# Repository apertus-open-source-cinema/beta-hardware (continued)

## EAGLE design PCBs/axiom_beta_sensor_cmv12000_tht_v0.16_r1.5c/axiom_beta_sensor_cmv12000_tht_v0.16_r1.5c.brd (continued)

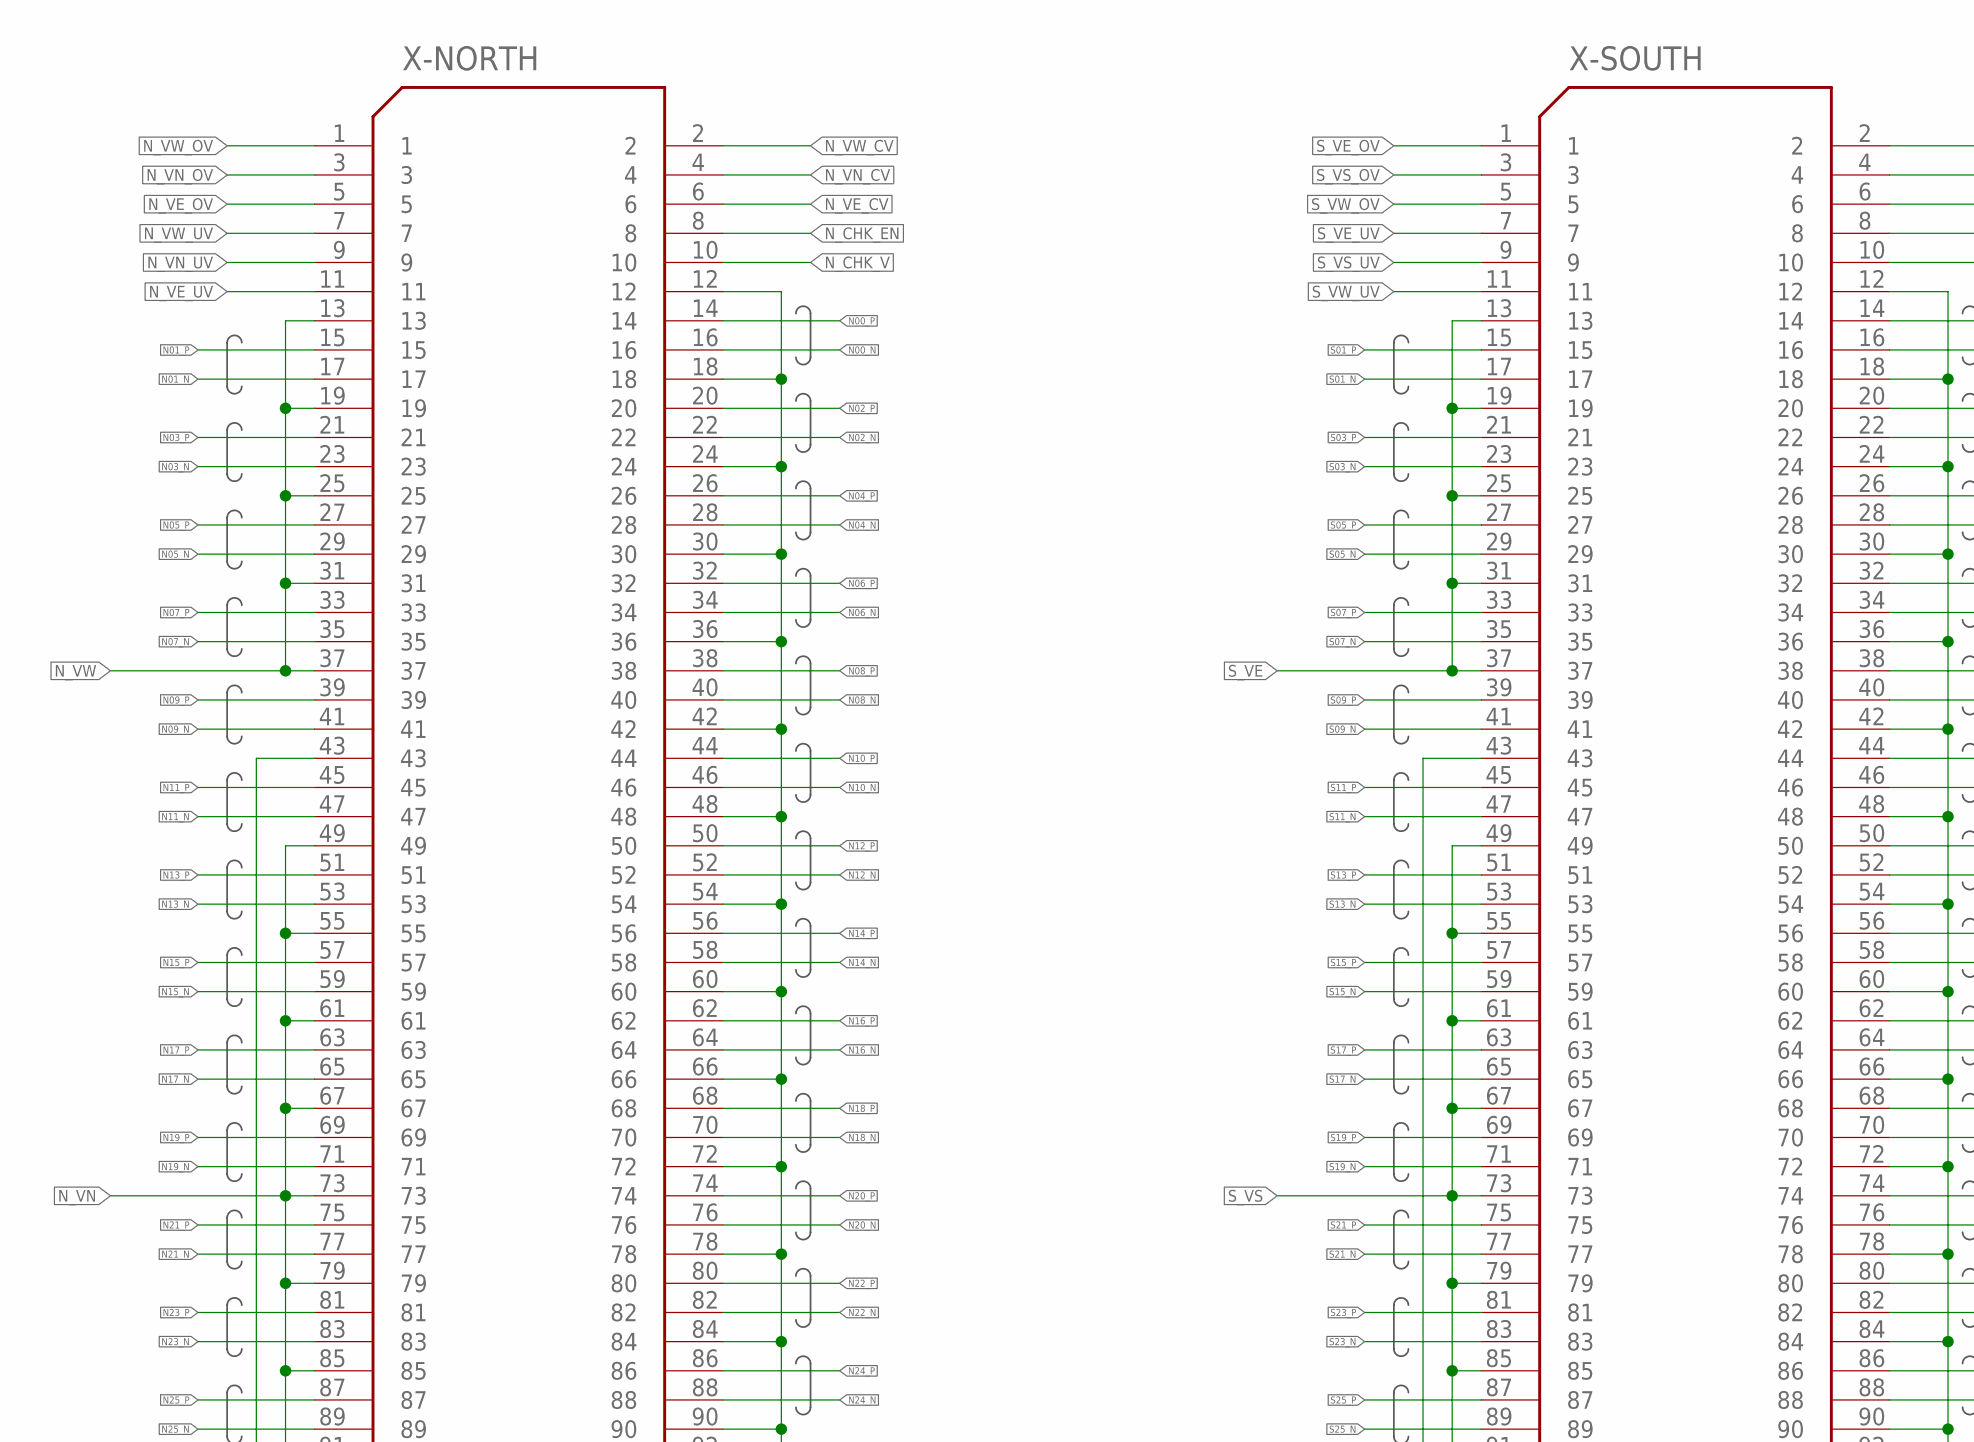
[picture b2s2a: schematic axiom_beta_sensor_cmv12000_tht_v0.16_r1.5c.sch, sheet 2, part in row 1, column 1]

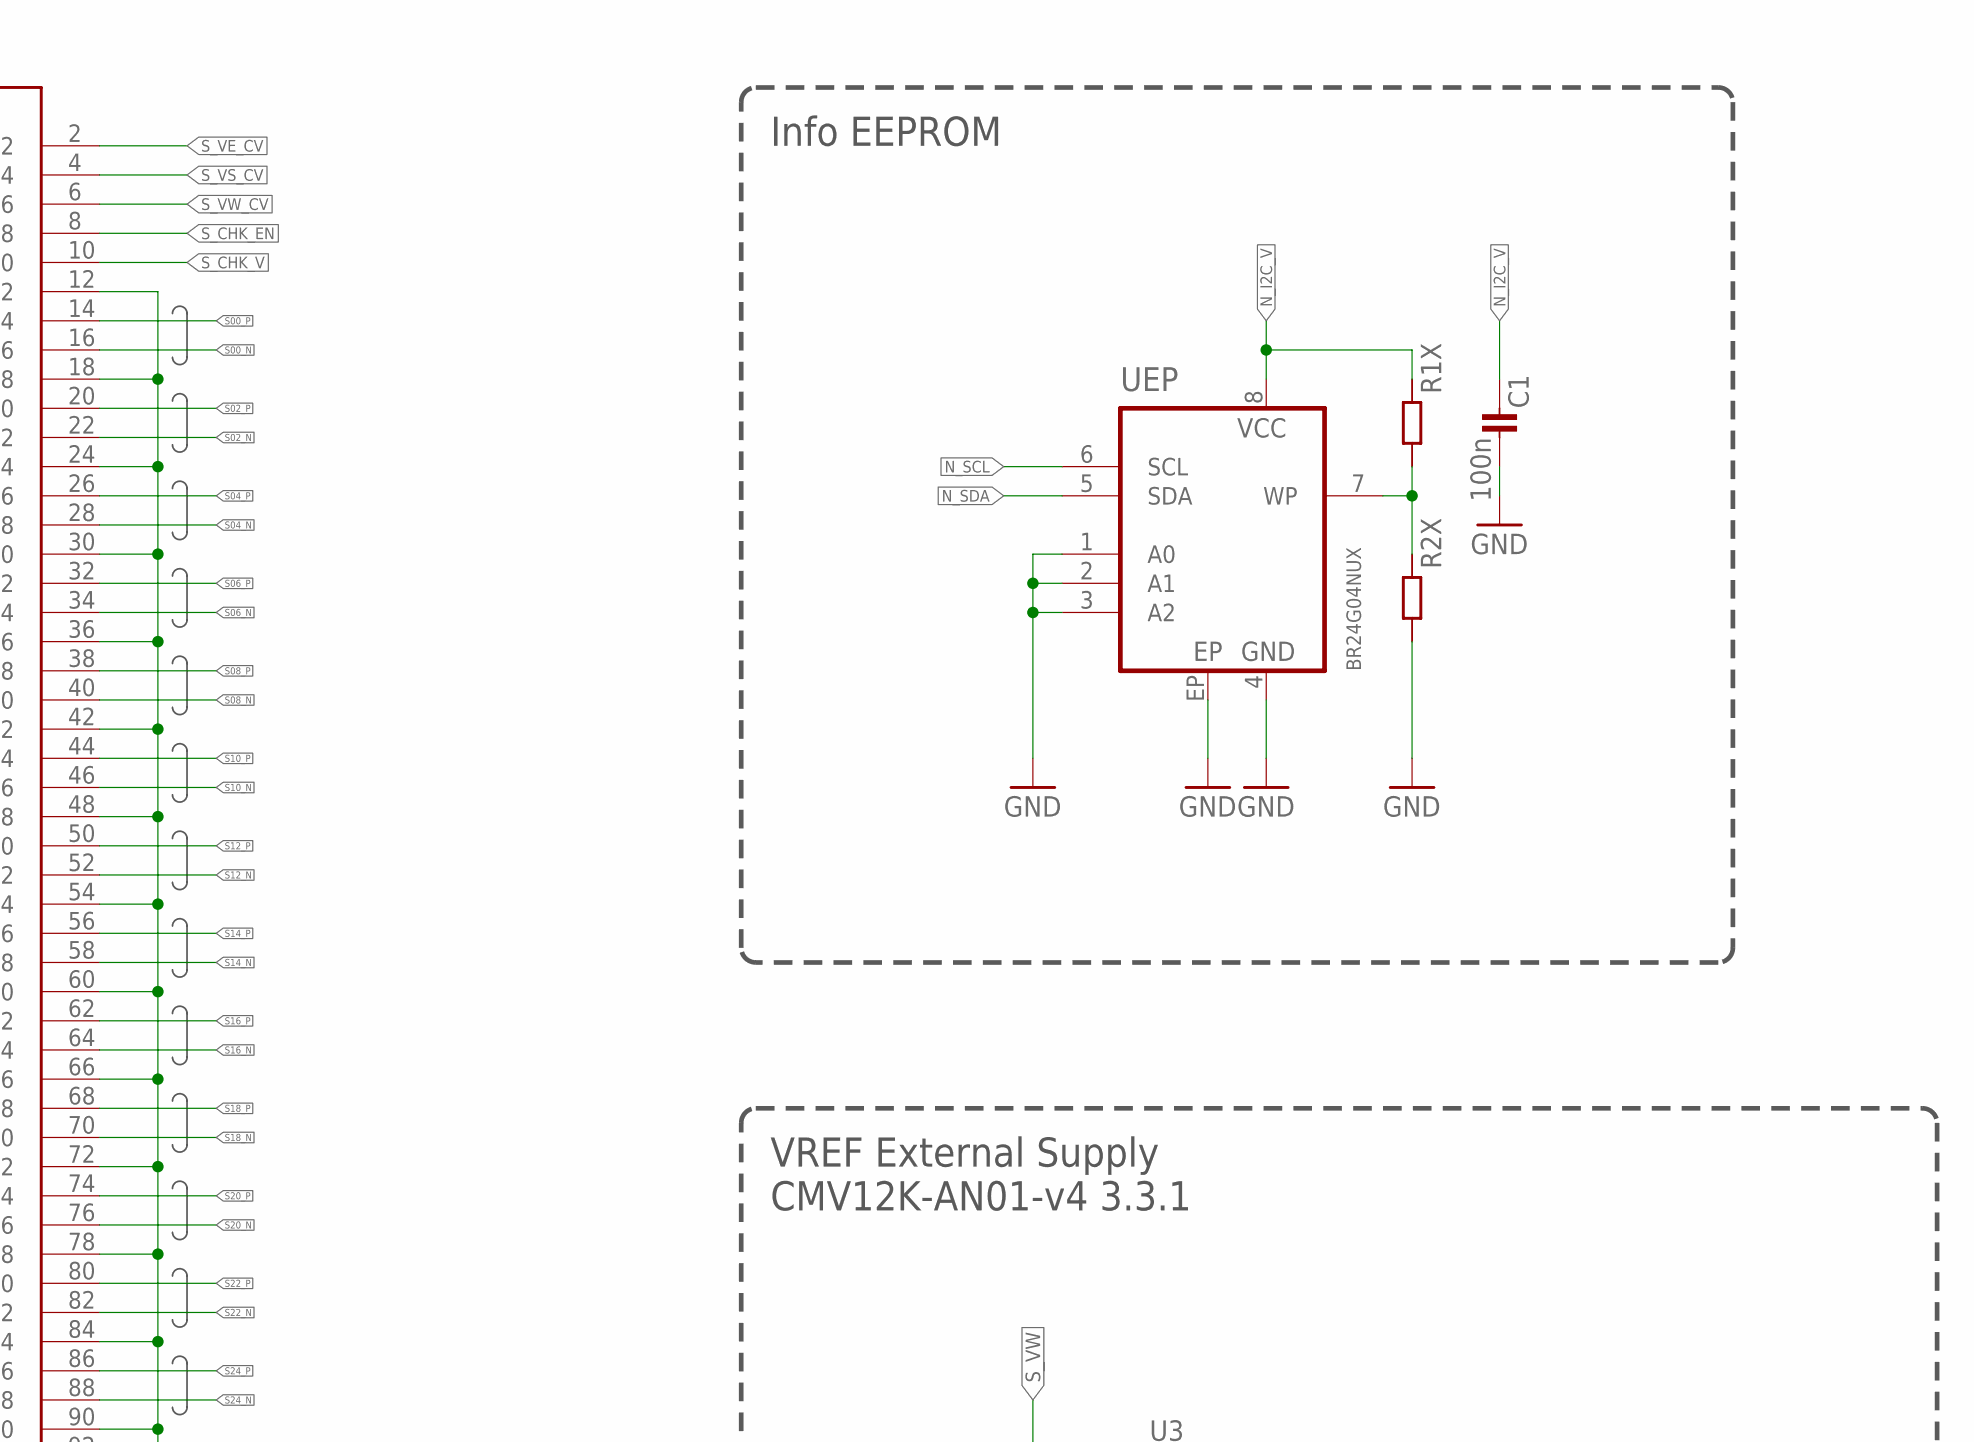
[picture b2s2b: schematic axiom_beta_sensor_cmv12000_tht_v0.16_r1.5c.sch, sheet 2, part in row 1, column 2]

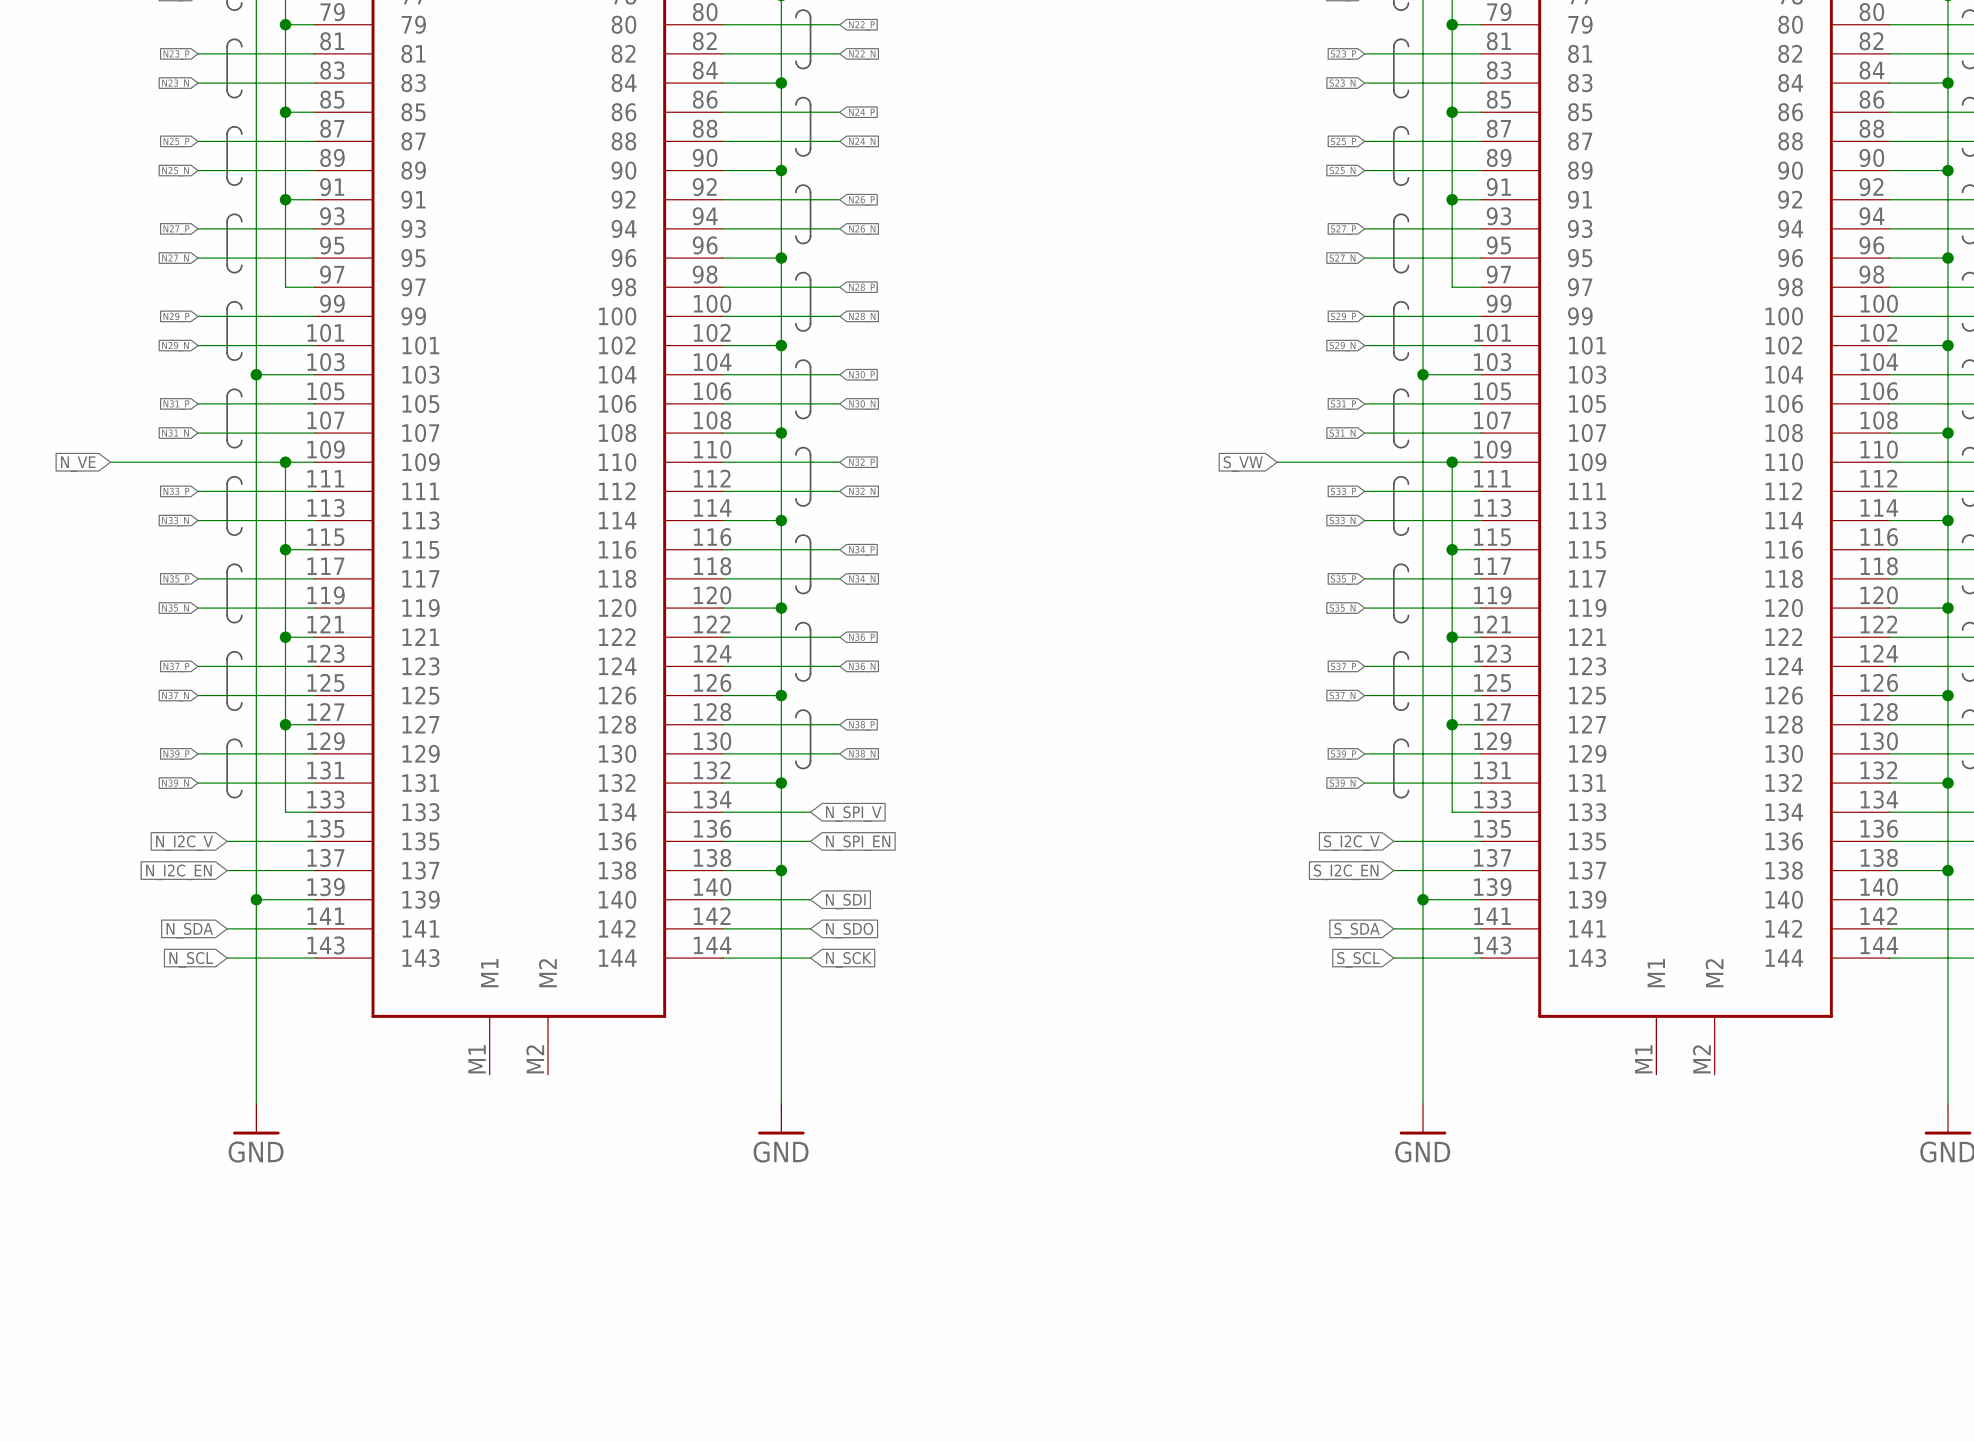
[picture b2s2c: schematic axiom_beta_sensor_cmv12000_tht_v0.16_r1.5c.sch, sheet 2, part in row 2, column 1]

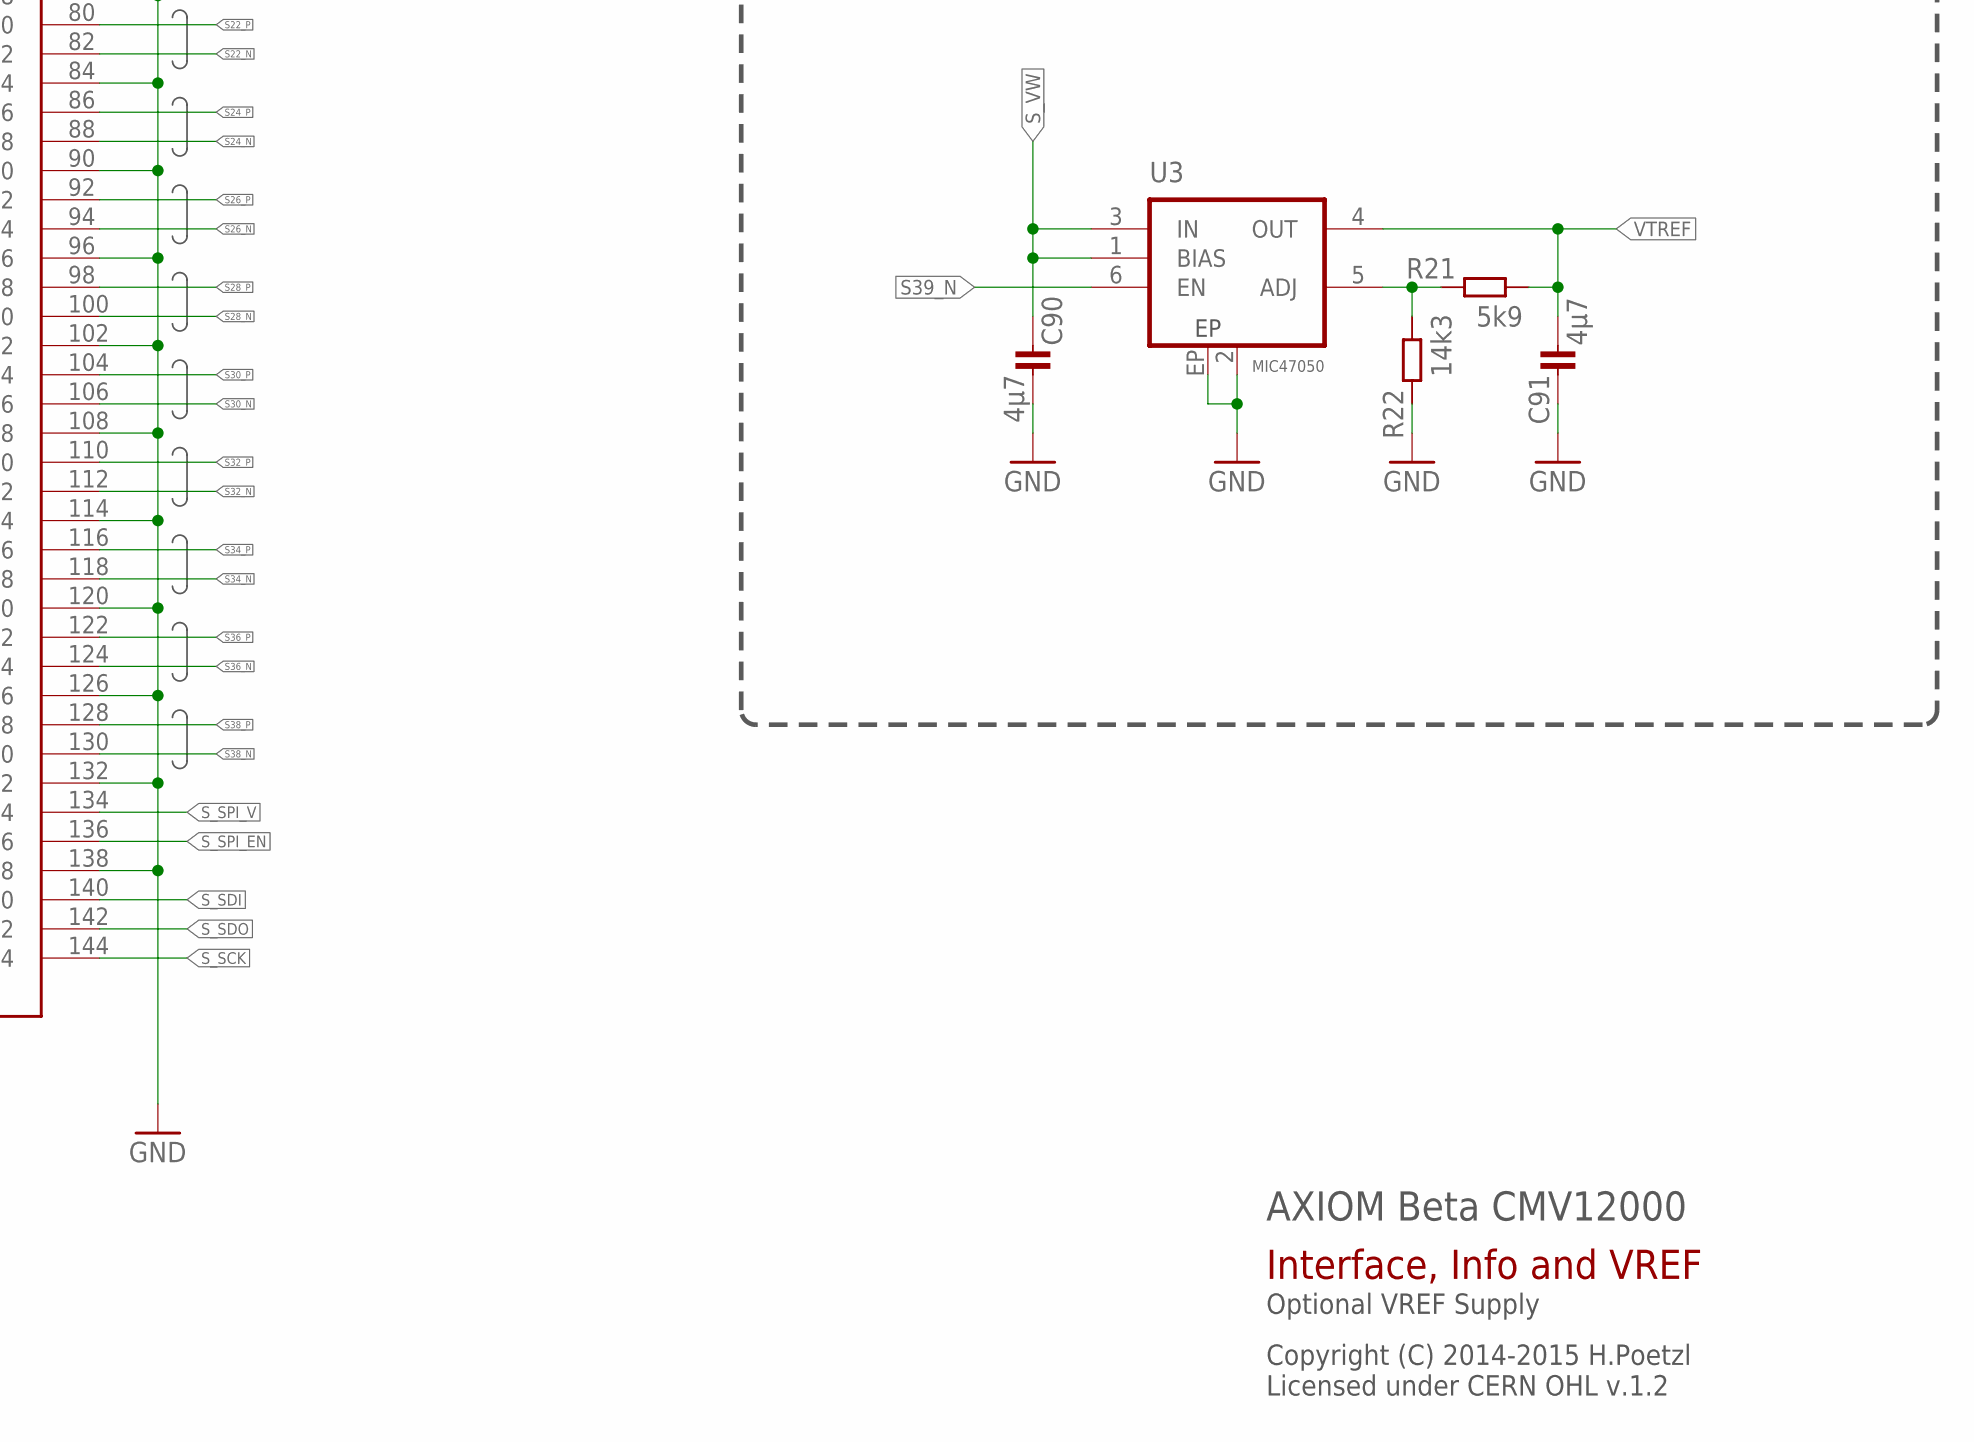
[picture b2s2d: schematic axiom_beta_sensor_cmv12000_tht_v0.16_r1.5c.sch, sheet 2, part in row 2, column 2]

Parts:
C1: 100n; 0402-C
C90, C91: 4µ7; 0402-C
R1X, R2X: R0402-C; 0402-C
R21: 5k9; 0402-C
R22: 14k3; 0402-C
U3: MIC47050; MLF-6
UEP: BR24G04NUX; DFN200X300X100-9N
X-NORTH: FX10-144P; FX10A-144P
X-SOUTH: FX10-144P; FX10A-144P

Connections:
GND: C1.2, C90.2, C91.1, R2X.2, R22.1, U3.2 (GND), U3.EP, UEP.1 (A0), UEP.2 (A1), UEP.3 (A2), UEP.4 (GND), UEP.EP, X-NORTH.12, X-NORTH.18, X-NORTH.24, X-NORTH.30, X-NORTH.36, X-NORTH.42, X-NORTH.43, X-NORTH.48, X-NORTH.54, X-NORTH.60, X-NORTH.66, X-NORTH.72, X-NORTH.78, X-NORTH.84, X-NORTH.90, X-NORTH.96, X-NORTH.102, X-NORTH.103, X-NORTH.108, X-NORTH.114, X-NORTH.120, X-NORTH.126, X-NORTH.132, X-NORTH.138, X-NORTH.139, X-SOUTH.12, X-SOUTH.18, X-SOUTH.24, X-SOUTH.30, X-SOUTH.36, X-SOUTH.42, X-SOUTH.43, X-SOUTH.48, X-SOUTH.54, X-SOUTH.60, X-SOUTH.66, X-SOUTH.72, X-SOUTH.78, X-SOUTH.84, X-SOUTH.90, X-SOUTH.96, X-SOUTH.102, X-SOUTH.103, X-SOUTH.108, X-SOUTH.114, X-SOUTH.120, X-SOUTH.126, X-SOUTH.132, X-SOUTH.138, X-SOUTH.139; also elsewhere on the board
N00_N: X-NORTH.16; also elsewhere on the board
N00_P: X-NORTH.14; also elsewhere on the board
N01_N: X-NORTH.17; also elsewhere on the board
N01_P: X-NORTH.15; also elsewhere on the board
N02_N: X-NORTH.22; also elsewhere on the board
N02_P: X-NORTH.20; also elsewhere on the board
N03_N: X-NORTH.23
N03_P: X-NORTH.21
N04_N: X-NORTH.28; also elsewhere on the board
N04_P: X-NORTH.26; also elsewhere on the board
N05_N: X-NORTH.29; also elsewhere on the board
N05_P: X-NORTH.27; also elsewhere on the board
N06_N: X-NORTH.34; also elsewhere on the board
N06_P: X-NORTH.32; also elsewhere on the board
N07_N: X-NORTH.35; also elsewhere on the board
N07_P: X-NORTH.33; also elsewhere on the board
N08_N: X-NORTH.40; also elsewhere on the board
N08_P: X-NORTH.38; also elsewhere on the board
N09_N: X-NORTH.41; also elsewhere on the board
N09_P: X-NORTH.39; also elsewhere on the board
N10_N: X-NORTH.46; also elsewhere on the board
N10_P: X-NORTH.44; also elsewhere on the board
N11_N: X-NORTH.47; also elsewhere on the board
N11_P: X-NORTH.45; also elsewhere on the board
N12_N: X-NORTH.52; also elsewhere on the board
N12_P: X-NORTH.50; also elsewhere on the board
N13_N: X-NORTH.53; also elsewhere on the board
N13_P: X-NORTH.51; also elsewhere on the board
N14_N: X-NORTH.58; also elsewhere on the board
N14_P: X-NORTH.56; also elsewhere on the board
N15_N: X-NORTH.59; also elsewhere on the board
N15_P: X-NORTH.57; also elsewhere on the board
N16_N: X-NORTH.64; also elsewhere on the board
N16_P: X-NORTH.62; also elsewhere on the board
N17_N: X-NORTH.65; also elsewhere on the board
N17_P: X-NORTH.63; also elsewhere on the board
N18_N: X-NORTH.70; also elsewhere on the board
N18_P: X-NORTH.68; also elsewhere on the board
N19_N: X-NORTH.71; also elsewhere on the board
N19_P: X-NORTH.69; also elsewhere on the board
N20_N: X-NORTH.76; also elsewhere on the board
N20_P: X-NORTH.74; also elsewhere on the board
N21_N: X-NORTH.77; also elsewhere on the board
N21_P: X-NORTH.75; also elsewhere on the board
N22_N: X-NORTH.82; also elsewhere on the board
N22_P: X-NORTH.80; also elsewhere on the board
N23_N: X-NORTH.83; also elsewhere on the board
N23_P: X-NORTH.81; also elsewhere on the board
N24_N: X-NORTH.88; also elsewhere on the board
N24_P: X-NORTH.86; also elsewhere on the board
N25_N: X-NORTH.89; also elsewhere on the board
N25_P: X-NORTH.87; also elsewhere on the board
N26_N: X-NORTH.94; also elsewhere on the board
N26_P: X-NORTH.92; also elsewhere on the board
N27_N: X-NORTH.95; also elsewhere on the board
N27_P: X-NORTH.93; also elsewhere on the board
N28_N: X-NORTH.100; also elsewhere on the board
N28_P: X-NORTH.98; also elsewhere on the board
N29_N: X-NORTH.101; also elsewhere on the board
N29_P: X-NORTH.99; also elsewhere on the board
N30_N: X-NORTH.106; also elsewhere on the board
N30_P: X-NORTH.104; also elsewhere on the board
N31_N: X-NORTH.107; also elsewhere on the board
N31_P: X-NORTH.105; also elsewhere on the board
N32_N: X-NORTH.112; also elsewhere on the board
N32_P: X-NORTH.110; also elsewhere on the board
N33_N: X-NORTH.113; also elsewhere on the board
N33_P: X-NORTH.111; also elsewhere on the board
N34_N: X-NORTH.118; also elsewhere on the board
N34_P: X-NORTH.116; also elsewhere on the board
N35_N: X-NORTH.119; also elsewhere on the board
N35_P: X-NORTH.117; also elsewhere on the board
N36_N: X-NORTH.124
N36_P: X-NORTH.122
N37_N: X-NORTH.125; also elsewhere on the board
N37_P: X-NORTH.123; also elsewhere on the board
N38_N: X-NORTH.130; also elsewhere on the board
N38_P: X-NORTH.128; also elsewhere on the board
N39_N: X-NORTH.131; also elsewhere on the board
N39_P: X-NORTH.129; also elsewhere on the board
unnamed: R1X.2, R2X.1, UEP.7 (WP)
unnamed: R21.1, R22.2, U3.5 (ADJ)
N_CHK_EN: X-NORTH.8
N_CHK_V: X-NORTH.10; also elsewhere on the board
N_I2C_EN: X-NORTH.137
N_I2C_V: C1.1, R1X.1, UEP.8 (VCC), X-NORTH.135
N_SCK: X-NORTH.144; also elsewhere on the board
N_SCL: UEP.6 (SCL), X-NORTH.143
N_SDA: UEP.5 (SDA), X-NORTH.141
N_SDI: X-NORTH.140; also elsewhere on the board
N_SDO: X-NORTH.142; also elsewhere on the board
N_SPI_EN: X-NORTH.136; also elsewhere on the board
N_SPI_V: X-NORTH.134; also elsewhere on the board
N_VE: X-NORTH.109, X-NORTH.115, X-NORTH.121, X-NORTH.127, X-NORTH.133; also elsewhere on the board
N_VE_CV: X-NORTH.6; also elsewhere on the board
N_VE_OV: X-NORTH.5; also elsewhere on the board
N_VE_UV: X-NORTH.11; also elsewhere on the board
N_VN: X-NORTH.49, X-NORTH.55, X-NORTH.61, X-NORTH.67, X-NORTH.73, X-NORTH.79, X-NORTH.85, X-NORTH.91, X-NORTH.97; also elsewhere on the board
N_VN_CV: X-NORTH.4; also elsewhere on the board
N_VN_OV: X-NORTH.3; also elsewhere on the board
N_VN_UV: X-NORTH.9; also elsewhere on the board
N_VW: X-NORTH.13, X-NORTH.19, X-NORTH.25, X-NORTH.31, X-NORTH.37; also elsewhere on the board
N_VW_CV: X-NORTH.2; also elsewhere on the board
N_VW_OV: X-NORTH.1; also elsewhere on the board
N_VW_UV: X-NORTH.7; also elsewhere on the board
S00_N: X-SOUTH.16
S00_P: X-SOUTH.14
S01_N: X-SOUTH.17
S01_P: X-SOUTH.15
S02_N: X-SOUTH.22
S02_P: X-SOUTH.20
S03_N: X-SOUTH.23
S03_P: X-SOUTH.21
S04_N: X-SOUTH.28; also elsewhere on the board
S04_P: X-SOUTH.26; also elsewhere on the board
S05_N: X-SOUTH.29
S05_P: X-SOUTH.27
S06_N: X-SOUTH.34; also elsewhere on the board
S06_P: X-SOUTH.32; also elsewhere on the board
S07_N: X-SOUTH.35; also elsewhere on the board
S07_P: X-SOUTH.33; also elsewhere on the board
S08_N: X-SOUTH.40; also elsewhere on the board
S08_P: X-SOUTH.38; also elsewhere on the board
S09_N: X-SOUTH.41; also elsewhere on the board
S09_P: X-SOUTH.39; also elsewhere on the board
S10_N: X-SOUTH.46; also elsewhere on the board
S10_P: X-SOUTH.44; also elsewhere on the board
S11_N: X-SOUTH.47; also elsewhere on the board
S11_P: X-SOUTH.45; also elsewhere on the board
S12_N: X-SOUTH.52; also elsewhere on the board
S12_P: X-SOUTH.50; also elsewhere on the board
S13_N: X-SOUTH.53; also elsewhere on the board
S13_P: X-SOUTH.51; also elsewhere on the board
S14_N: X-SOUTH.58; also elsewhere on the board
S14_P: X-SOUTH.56; also elsewhere on the board
S15_N: X-SOUTH.59; also elsewhere on the board
S15_P: X-SOUTH.57; also elsewhere on the board
S16_N: X-SOUTH.64; also elsewhere on the board
S16_P: X-SOUTH.62; also elsewhere on the board
S17_N: X-SOUTH.65; also elsewhere on the board
S17_P: X-SOUTH.63; also elsewhere on the board
S18_N: X-SOUTH.70; also elsewhere on the board
S18_P: X-SOUTH.68; also elsewhere on the board
S19_N: X-SOUTH.71; also elsewhere on the board
S19_P: X-SOUTH.69; also elsewhere on the board
S20_N: X-SOUTH.76; also elsewhere on the board
S20_P: X-SOUTH.74; also elsewhere on the board
S21_N: X-SOUTH.77; also elsewhere on the board
S21_P: X-SOUTH.75; also elsewhere on the board
S22_N: X-SOUTH.82; also elsewhere on the board
S22_P: X-SOUTH.80; also elsewhere on the board
S23_N: X-SOUTH.83; also elsewhere on the board
S23_P: X-SOUTH.81; also elsewhere on the board
S24_N: X-SOUTH.88; also elsewhere on the board
S24_P: X-SOUTH.86; also elsewhere on the board
S25_N: X-SOUTH.89; also elsewhere on the board
S25_P: X-SOUTH.87; also elsewhere on the board
S26_N: X-SOUTH.94; also elsewhere on the board
S26_P: X-SOUTH.92; also elsewhere on the board
S27_N: X-SOUTH.95; also elsewhere on the board
S27_P: X-SOUTH.93; also elsewhere on the board
S28_N: X-SOUTH.100; also elsewhere on the board
S28_P: X-SOUTH.98; also elsewhere on the board
S29_N: X-SOUTH.101; also elsewhere on the board
S29_P: X-SOUTH.99; also elsewhere on the board
S30_N: X-SOUTH.106; also elsewhere on the board
S30_P: X-SOUTH.104; also elsewhere on the board
S31_N: X-SOUTH.107; also elsewhere on the board
S31_P: X-SOUTH.105; also elsewhere on the board
S32_N: X-SOUTH.112; also elsewhere on the board
S32_P: X-SOUTH.110; also elsewhere on the board
S33_N: X-SOUTH.113; also elsewhere on the board
S33_P: X-SOUTH.111; also elsewhere on the board
S34_N: X-SOUTH.118; also elsewhere on the board
S34_P: X-SOUTH.116; also elsewhere on the board
S35_N: X-SOUTH.119; also elsewhere on the board
S35_P: X-SOUTH.117; also elsewhere on the board
S36_N: X-SOUTH.124; also elsewhere on the board
S36_P: X-SOUTH.122; also elsewhere on the board
S37_N: X-SOUTH.125; also elsewhere on the board
S37_P: X-SOUTH.123; also elsewhere on the board
S38_N: X-SOUTH.130
S38_P: X-SOUTH.128
S39_N: U3.6 (EN), X-SOUTH.131
S39_P: X-SOUTH.129
S_CHK_EN: X-SOUTH.8
S_CHK_V: X-SOUTH.10; also elsewhere on the board
S_I2C_EN: X-SOUTH.137
S_I2C_V: X-SOUTH.135; also elsewhere on the board
S_SCK: X-SOUTH.144
S_SCL: X-SOUTH.143; also elsewhere on the board
S_SDA: X-SOUTH.141; also elsewhere on the board
S_SDI: X-SOUTH.140
S_SDO: X-SOUTH.142
S_SPI_EN: X-SOUTH.136
S_SPI_V: X-SOUTH.134
S_VE: X-SOUTH.13, X-SOUTH.19, X-SOUTH.25, X-SOUTH.31, X-SOUTH.37
S_VE_CV: X-SOUTH.2; also elsewhere on the board
S_VE_OV: X-SOUTH.1; also elsewhere on the board
S_VE_UV: X-SOUTH.7; also elsewhere on the board
S_VS: X-SOUTH.49, X-SOUTH.55, X-SOUTH.61, X-SOUTH.67, X-SOUTH.73, X-SOUTH.79, X-SOUTH.85, X-SOUTH.91, X-SOUTH.97; also elsewhere on the board
S_VS_CV: X-SOUTH.4; also elsewhere on the board
S_VS_OV: X-SOUTH.3; also elsewhere on the board
S_VS_UV: X-SOUTH.9; also elsewhere on the board
S_VW: C90.1, U3.1 (BIAS), U3.3 (IN), X-SOUTH.109, X-SOUTH.115, X-SOUTH.121, X-SOUTH.127, X-SOUTH.133
S_VW_CV: X-SOUTH.6; also elsewhere on the board
S_VW_OV: X-SOUTH.5; also elsewhere on the board
S_VW_UV: X-SOUTH.11; also elsewhere on the board
VTREF: C91.2, R21.2, U3.4 (OUT); also elsewhere on the board

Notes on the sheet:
Info EEPROM
VREF External Supply CMV12K-AN01-v4 3.3.1
AXIOM Beta CMV12000
Copyright (C) 2014-2015 H.Poetzl Licensed under CERN OHL v.1.2
Interface, Info and VREF
Optional VREF Supply

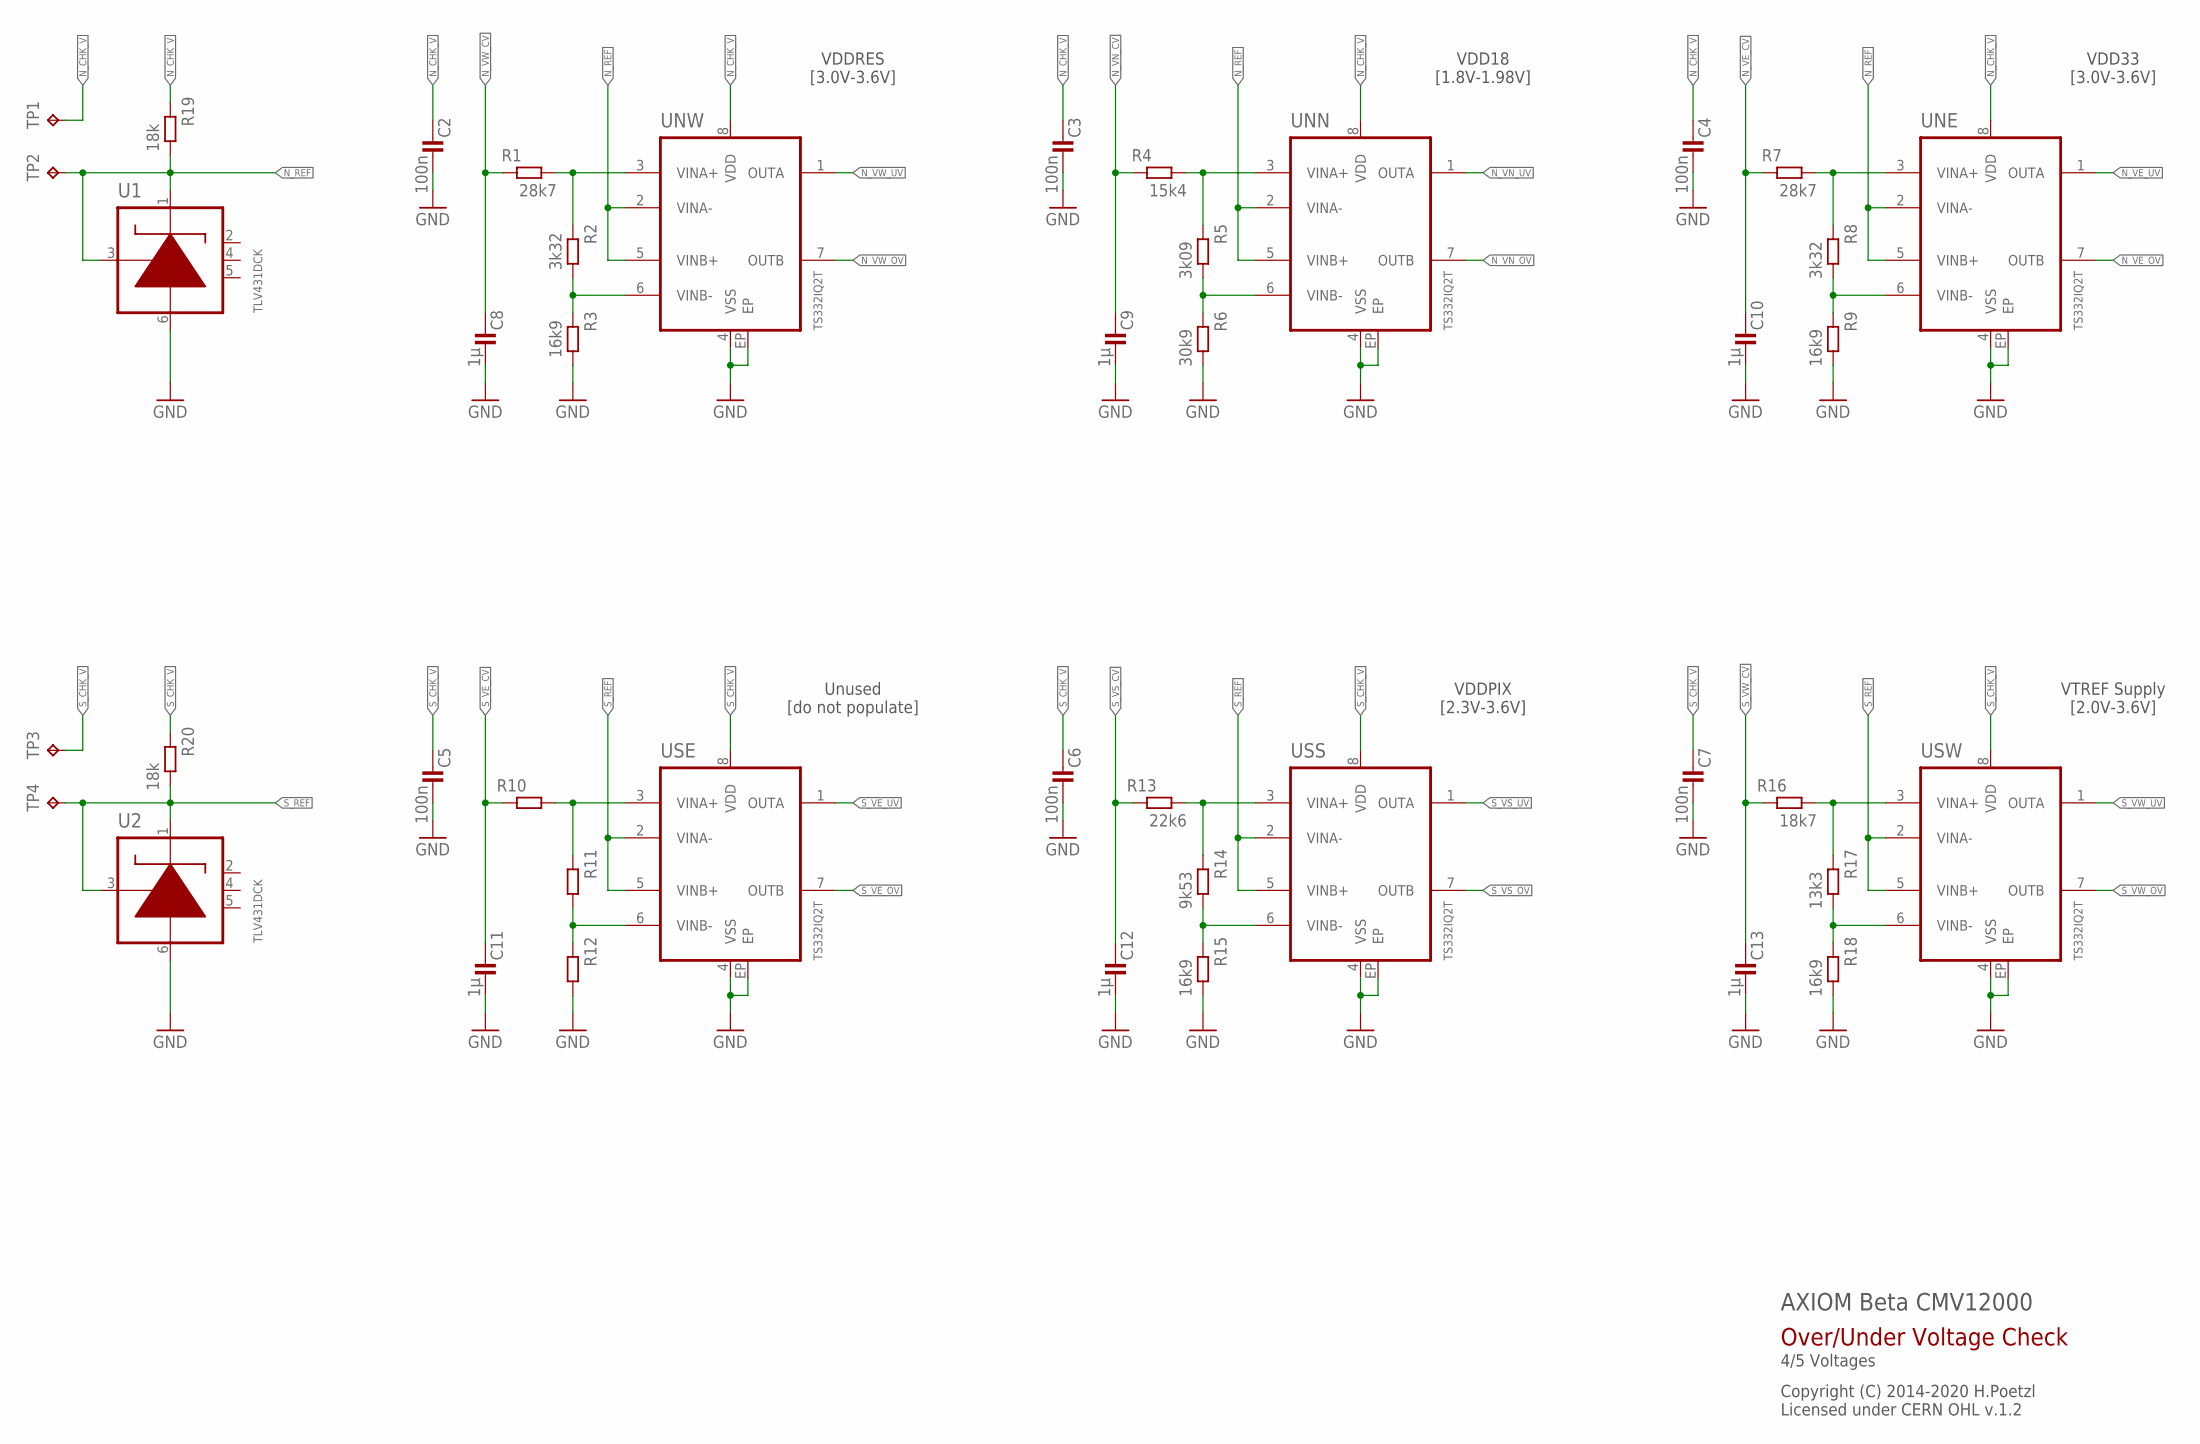
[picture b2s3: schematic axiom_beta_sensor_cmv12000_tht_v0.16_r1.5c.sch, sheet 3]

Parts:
C2, C3, C4, C5, C6, C7: 100n; 0402-C
C8, C9, C10, C11, C12, C13: 1µ; 0402-C
R1, R7: 28k7; 0402-C
R2, R8: 3k32; 0402-C
R3, R9, R15, R18: 16k9; 0402-C
R4: 15k4; 0402-C
R5: 3k09; 0402-C
R6: 30k9; 0402-C
R10, R11, R12: R0402-C; 0402-C
R13: 22k6; 0402-C
R14: 9k53; 0402-C
R16: 18k7; 0402-C
R17: 13k3; 0402-C
R19, R20: 18k; 0402-C
TP1, TP2, TP3, TP4: TPTP10R; TP10R
U1, U2: TLV431DCK; SOT65P210X110-6N
UNE: TS332IQ2T; DFN200X200X100-9N
UNN: TS332IQ2T; DFN200X200X100-9N
UNW: TS332IQ2T; DFN200X200X100-9N
USE: TS332IQ2T; DFN200X200X100-9N
USS: TS332IQ2T; DFN200X200X100-9N
USW: TS332IQ2T; DFN200X200X100-9N

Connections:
GND: C2.2, C3.2, C4.2, C5.2, C6.2, C7.2, C8.2, C9.2, C10.2, C11.2, C12.2, C13.2, R3.2, R6.2, R9.2, R12.2, R15.2, R18.2, U1.6 (ANODE), U2.6 (ANODE), UNE.4 (VSS), UNE.EP, UNN.4 (VSS), UNN.EP, UNW.4 (VSS), UNW.EP, USE.4 (VSS), USE.EP, USS.4 (VSS), USS.EP, USW.4 (VSS), USW.EP; also elsewhere on the board
unnamed: R11.2, R12.1, USE.6 (VINB-)
unnamed: R5.2, R6.1, UNN.6 (VINB-)
unnamed: R8.2, R9.1, UNE.6 (VINB-)
unnamed: R10.2, R11.1, USE.3 (VINA+)
unnamed: R7.2, R8.1, UNE.3 (VINA+)
unnamed: R1.2, R2.1, UNW.3 (VINA+)
unnamed: R2.2, R3.1, UNW.6 (VINB-)
unnamed: R14.2, R15.1, USS.6 (VINB-)
unnamed: R13.2, R14.1, USS.3 (VINA+)
unnamed: R16.2, R17.1, USW.3 (VINA+)
unnamed: R17.2, R18.1, USW.6 (VINB-)
N_CHK_V: C2.1, C3.1, C4.1, R19.1, TP1.TP, UNE.8 (VDD), UNN.8 (VDD), UNW.8 (VDD); also elsewhere on the board
N_REF: R19.2, TP2.TP, U1.1 (CATHODE), U1.3 (REF), UNE.2 (VINA-), UNE.5 (VINB+), UNN.2 (VINA-), UNN.5 (VINB+), UNW.2 (VINA-), UNW.5 (VINB+)
N_VE_CV: C10.1, R7.1; also elsewhere on the board
N_VE_OV: UNE.7 (OUTB); also elsewhere on the board
N_VE_UV: UNE.1 (OUTA); also elsewhere on the board
N_VN_CV: C9.1, R4.1; also elsewhere on the board
N_VN_OV: UNN.7 (OUTB); also elsewhere on the board
N_VN_UV: UNN.1 (OUTA); also elsewhere on the board
N_VW_CV: C8.1, R1.1; also elsewhere on the board
N_VW_OV: UNW.7 (OUTB); also elsewhere on the board
N_VW_UV: UNW.1 (OUTA); also elsewhere on the board
R5: R4.2, R5.1, UNN.3 (VINA+)
S_CHK_V: C5.1, C6.1, C7.1, R20.1, TP3.TP, USE.8 (VDD), USS.8 (VDD), USW.8 (VDD); also elsewhere on the board
S_REF: R20.2, TP4.TP, U2.1 (CATHODE), U2.3 (REF), USE.2 (VINA-), USE.5 (VINB+), USS.2 (VINA-), USS.5 (VINB+), USW.2 (VINA-), USW.5 (VINB+)
S_VE_CV: C11.1, R10.1; also elsewhere on the board
S_VE_OV: USE.7 (OUTB); also elsewhere on the board
S_VE_UV: USE.1 (OUTA); also elsewhere on the board
S_VS_CV: C12.1, R13.1; also elsewhere on the board
S_VS_OV: USS.7 (OUTB); also elsewhere on the board
S_VS_UV: USS.1 (OUTA); also elsewhere on the board
S_VW_CV: C13.1, R16.1; also elsewhere on the board
S_VW_OV: USW.7 (OUTB); also elsewhere on the board
S_VW_UV: USW.1 (OUTA); also elsewhere on the board

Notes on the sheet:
AXIOM Beta CMV12000
Copyright (C) 2014-2020 H.Poetzl Licensed under CERN OHL v.1.2
Over/Under Voltage Check
4/5 Voltages
VDDRES [3.0V-3.6V]
VDD18 [1.8V-1.98V]
VDD33 [3.0V-3.6V]
VDDPIX [2.3V-3.6V]
VTREF Supply [2.0V-3.6V]
Unused [do not populate]
